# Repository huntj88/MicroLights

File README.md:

When submitting to factory, make sure USER.1 kicad layer is included in v-cut layers. On JLCPCB this is done with a PCB Remark note under advanced options section

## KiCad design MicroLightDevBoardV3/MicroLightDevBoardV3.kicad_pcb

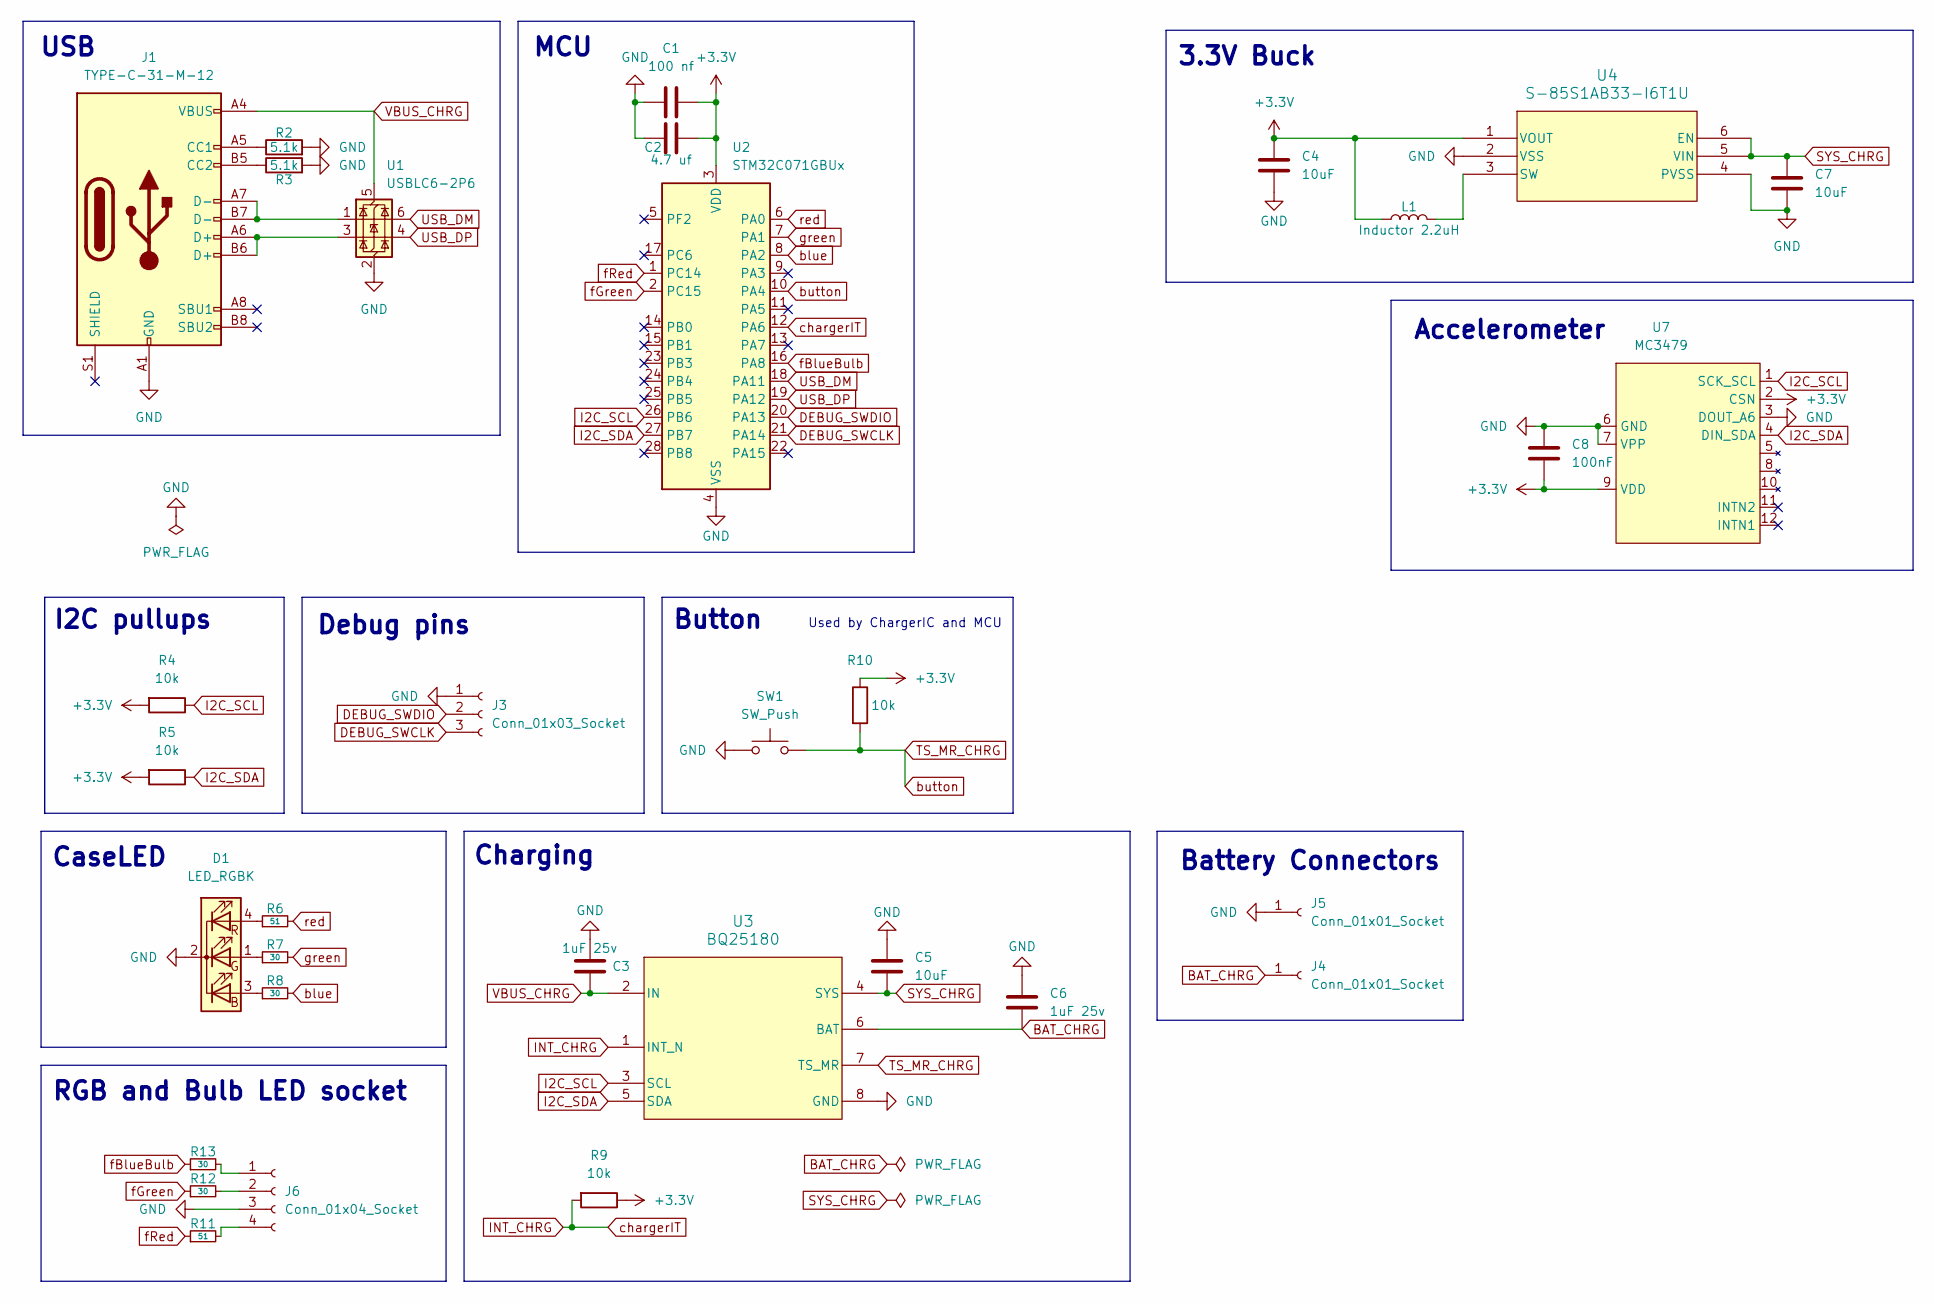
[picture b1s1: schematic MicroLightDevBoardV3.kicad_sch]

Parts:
C1: 100 nf; C_0402_1005Metric; LCSC C1525
C2: 4.7 uf; C_0402_1005Metric; LCSC C23733
C3, C6: 1uF 25v; C_0402_1005Metric; LCSC C52923
C4, C5, C7: 10uF; C_0402_1005Metric; LCSC C15525
C8: 100nF; C_0402_1005Metric; LCSC C1525
D1: LED_RGBK; RS-C1415MBAR; LCSC C2874181
J1: TYPE-C-31-M-12; USB_C_Receptacle_Hroparts_TYPE-C-31-M-12; LCSC C165948
J3: Conn_01x03_Socket; Microlight_debug_pins
J4, J5: Conn_01x01_Socket; battery_1x01_Vertical
J6: Conn_01x04_Socket; rgbLed4Pin_1.27mm
L1: Inductor 2.2uH; 74438343022_L; LCSC C337891
R2, R3: 5.1k; R_0402_1005Metric; LCSC C25905
R4, R5, R9, R10: 10k; R_0402_1005Metric; LCSC C25744
R6, R11: 51; R_0402_1005Metric; LCSC C25125
R7, R8, R12, R13: 30; R_0402_1005Metric; LCSC C270617
SW1: SW_Push; TS-1089S-02526; LCSC C455282
U1: USBLC6-2P6; SOT-666; LCSC C3647099
U2: STM32C071GBUx; QFN-28_4x4mm_P0.5mm; LCSC C42113261
U3: BQ25180; LCSC C3682423
U4: S-85S1AB33-I6T1U; SNT-6A-A-PKG_PG006-A-P-SD-2.1_ABL; LCSC C7070110
U7: MC3479; LGA-12_2x2mm_P0.5mm

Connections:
+3.3V: C1.1, C2.1, C4.1, C8.2, L1.1, R4.2, R5.2, R9.1, R10.1, U2.3 (VDD), U4.1 (VOUT), U7.2 (CSN), U7.9 (VDD)
BAT_CHRG: C6.2, J4.1, U3.6 (BAT)
DEBUG_SWCLK: J3.3, U2.21 (PA14)
DEBUG_SWDIO: J3.2, U2.20 (PA13)
GND: C1.2, C2.2, C3.1, C4.2, C5.1, C6.1, C7.2, C8.1, D1.2 (K), J1.A1 (GND), J1.B1 (GND), J3.1, J5.1, J6.3, R2.2, R3.2, SW1.1, U1.2 (GND), U2.4 (VSS), U3.8 (GND), U4.2 (VSS), U4.4 (PVSS), U7.3 (DOUT_A6), U7.6 (GND), U7.7 (VPP)
I2C_SCL: R4.1, U2.26 (PB6), U3.3 (SCL), U7.1 (SCK_SCL)
I2C_SDA: R5.1, U2.27 (PB7), U3.5 (SDA), U7.4 (DIN_SDA)
INT_CHRG: R9.2, U2.12 (PA6), U3.1 (INT_N)
unnamed: D1.3 (BA), R8.1
unnamed: D1.1 (GA), R7.1
unnamed: D1.4 (RA), R6.1
unnamed: J1.A5 (CC1), R2.1
unnamed: J1.B5 (CC2), R3.1
unnamed: J1.A6 (D+), J1.B6 (D+), U1.3 (I/O2)
unnamed: J1.A7 (D-), J1.B7 (D-), U1.1 (I/O1)
unnamed: J6.1, R13.2
unnamed: J6.2, R12.2
unnamed: J6.4, R11.2
unnamed: L1.2, U4.3 (SW)
SYS_CHRG: C5.2, C7.1, U3.4 (SYS), U4.5 (VIN), U4.6 (EN)
TS_MR_CHRG: R10.2, SW1.2, U2.10 (PA4), U3.7 (TS_MR)
USB_DM: U1.6 (I/O1), U2.18 (PA11)
USB_DP: U1.4 (I/O2), U2.19 (PA12)
VBUS_CHRG: C3.2, J1.A4 (VBUS), J1.B4 (VBUS), U1.5 (VBUS), U3.2 (IN)
blue: R8.2, U2.8 (PA2)
fBlueBulb: R13.1, U2.16 (PA8)
fGreen: R12.1, U2.2 (PC15)
fRed: R11.1, U2.1 (PC14)
green: R7.2, U2.7 (PA1)
red: R6.2, U2.6 (PA0)

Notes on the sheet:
Used by ChargerIC and MCU
I2C pullups
CaseLED
RGB and Bulb LED socket
USB
Charging
3.3V Buck
Accelerometer
Battery Connectors
Debug pins
Button
MCU

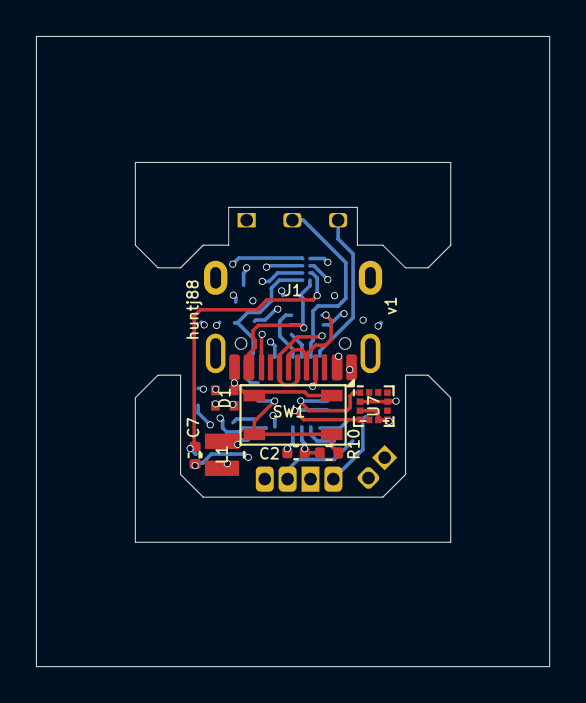
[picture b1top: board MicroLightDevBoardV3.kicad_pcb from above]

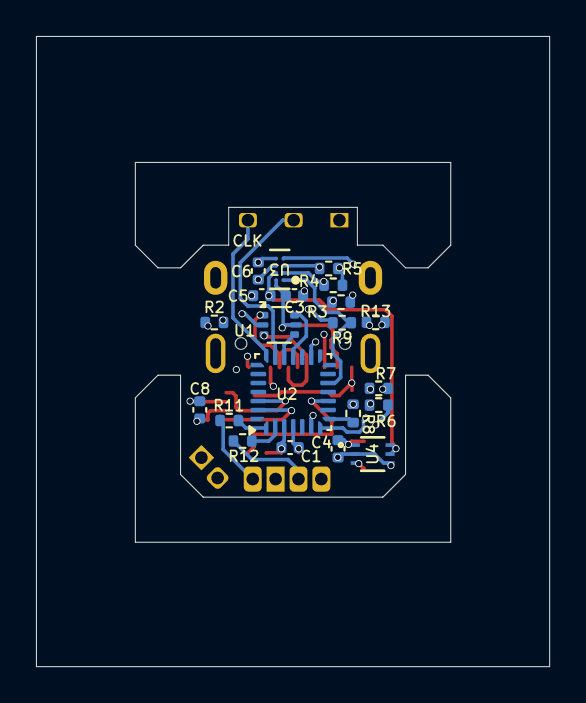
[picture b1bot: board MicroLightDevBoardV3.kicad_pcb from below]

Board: 6 copper layers, 28.5 x 35.0 mm, 33 parts (21 on the bottom side), 30 nets.

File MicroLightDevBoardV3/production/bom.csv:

Designator,Footprint,Quantity,Value,LCSC Part #
C1,0402,1,100 nf,C1525
C2,0402,1,4.7 uf,C23733
"C3, C6",0402,2,1uF 25v,C52923
"C4, C5, C7",0402,3,10uF,C15525
C8,0402,1,100nF,C1525
D1,RS-C1415MBAR,1,LED_RGBK,C2874181
J1,USB_C_Receptacle_Hroparts_TYPE-C-31-M-12,1,TYPE-C-31-M-12,C165948
L1,74438343022_L,1,Inductor 2.2uH,C337891
"R10, R4, R5, R9",0402,4,10k,C25744
"R11, R6",0402,2,51,C25125
"R12, R13, R7, R8",0402,4,30,C270617
"R2, R3",0402,2,5.1k,C25905
SW1,TS-1089S-02526,1,SW_Push,C455282
U1,SOT-666,1,USBLC6-2P6,C3647099
U2,QFN-28_4x4mm_P0.5mm,1,STM32C071GBUx,C42113261
U3,BQ25180,1,BQ25180,C3682423
U4,SNT-6A-A-PKG_PG006-A-P-SD-2.1_ABL,1,S-85S1AB33-I6T1U,C7070110
U7,LGA-12_2x2mm_P0.5mm,1,MC3479,

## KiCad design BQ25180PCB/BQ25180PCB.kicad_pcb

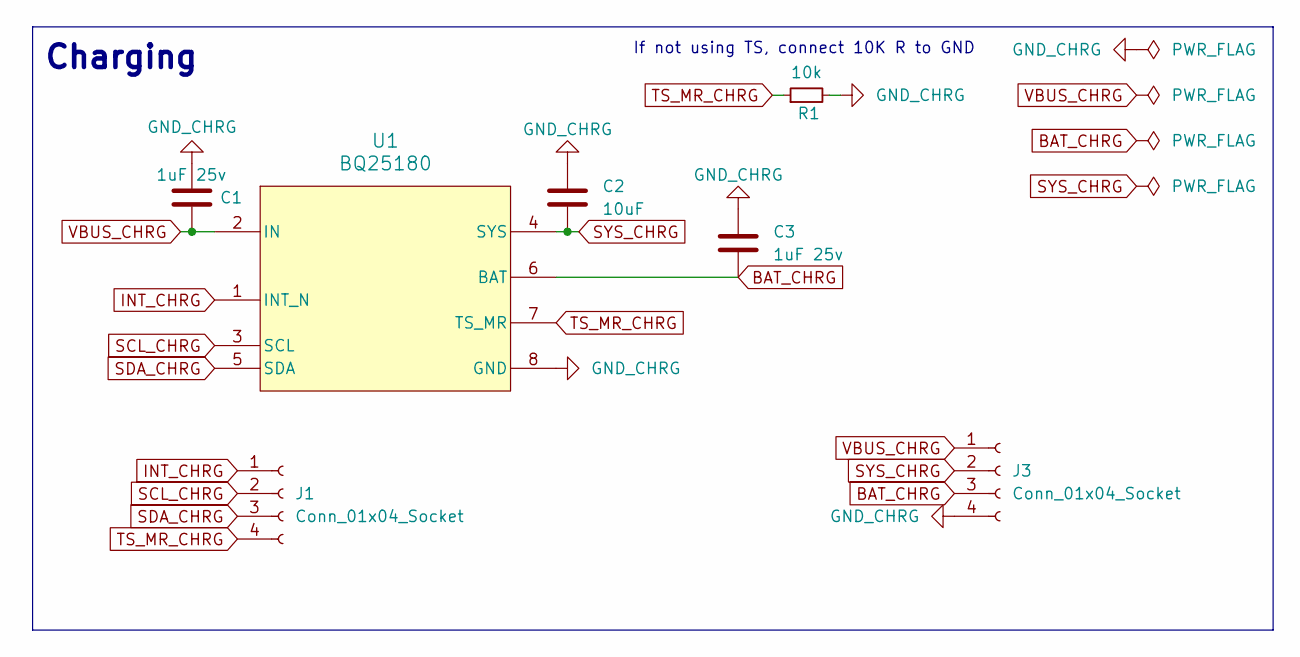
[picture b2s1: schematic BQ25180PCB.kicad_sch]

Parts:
C1, C3: 1uF 25v; C_0805_2012Metric; LCSC C1712
C2: 10uF; C_0805_2012Metric; LCSC C15850
J1, J3: Conn_01x04_Socket; PinSocket_1x04_P2.54mm_Vertical; LCSC C2718488
R1: 10k; R_0805_2012Metric; LCSC C17414
U1: BQ25180; LCSC C3682423

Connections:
BAT_CHRG: C3.2, J3.3, U1.6 (BAT)
GND_CHRG: C1.1, C2.1, C3.1, J3.4, R1.2, U1.8 (GND)
INT_CHRG: J1.1, U1.1 (INT_N)
SCL_CHRG: J1.2, U1.3 (SCL)
SDA_CHRG: J1.3, U1.5 (SDA)
SYS_CHRG: C2.2, J3.2, U1.4 (SYS)
TS_MR_CHRG: J1.4, R1.1, U1.7 (TS_MR)
VBUS_CHRG: C1.2, J3.1, U1.2 (IN)

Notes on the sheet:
If not using TS, connect 10K R to GND
Charging

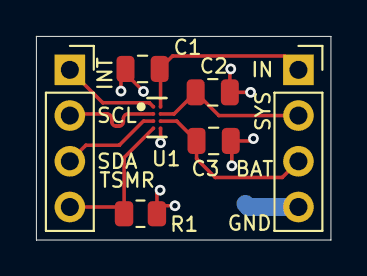
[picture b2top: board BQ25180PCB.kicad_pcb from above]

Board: 2 copper layers, 16.4 x 11.3 mm, 7 parts (0 on the bottom side), 8 nets.

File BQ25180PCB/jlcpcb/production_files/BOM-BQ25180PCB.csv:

Comment,Designator,Footprint,LCSC
10uF,C2,C_0805_2012Metric,C15850
1uF 25v,"C1,C3",C_0805_2012Metric,C1712
10k,R1,R_0805_2012Metric,C17414
Conn_01x04_Socket,"J1,J3",PinSocket_1x04_P2.54mm_Vertical,C2718488
BQ25180,U1,BQ25180,C3682423

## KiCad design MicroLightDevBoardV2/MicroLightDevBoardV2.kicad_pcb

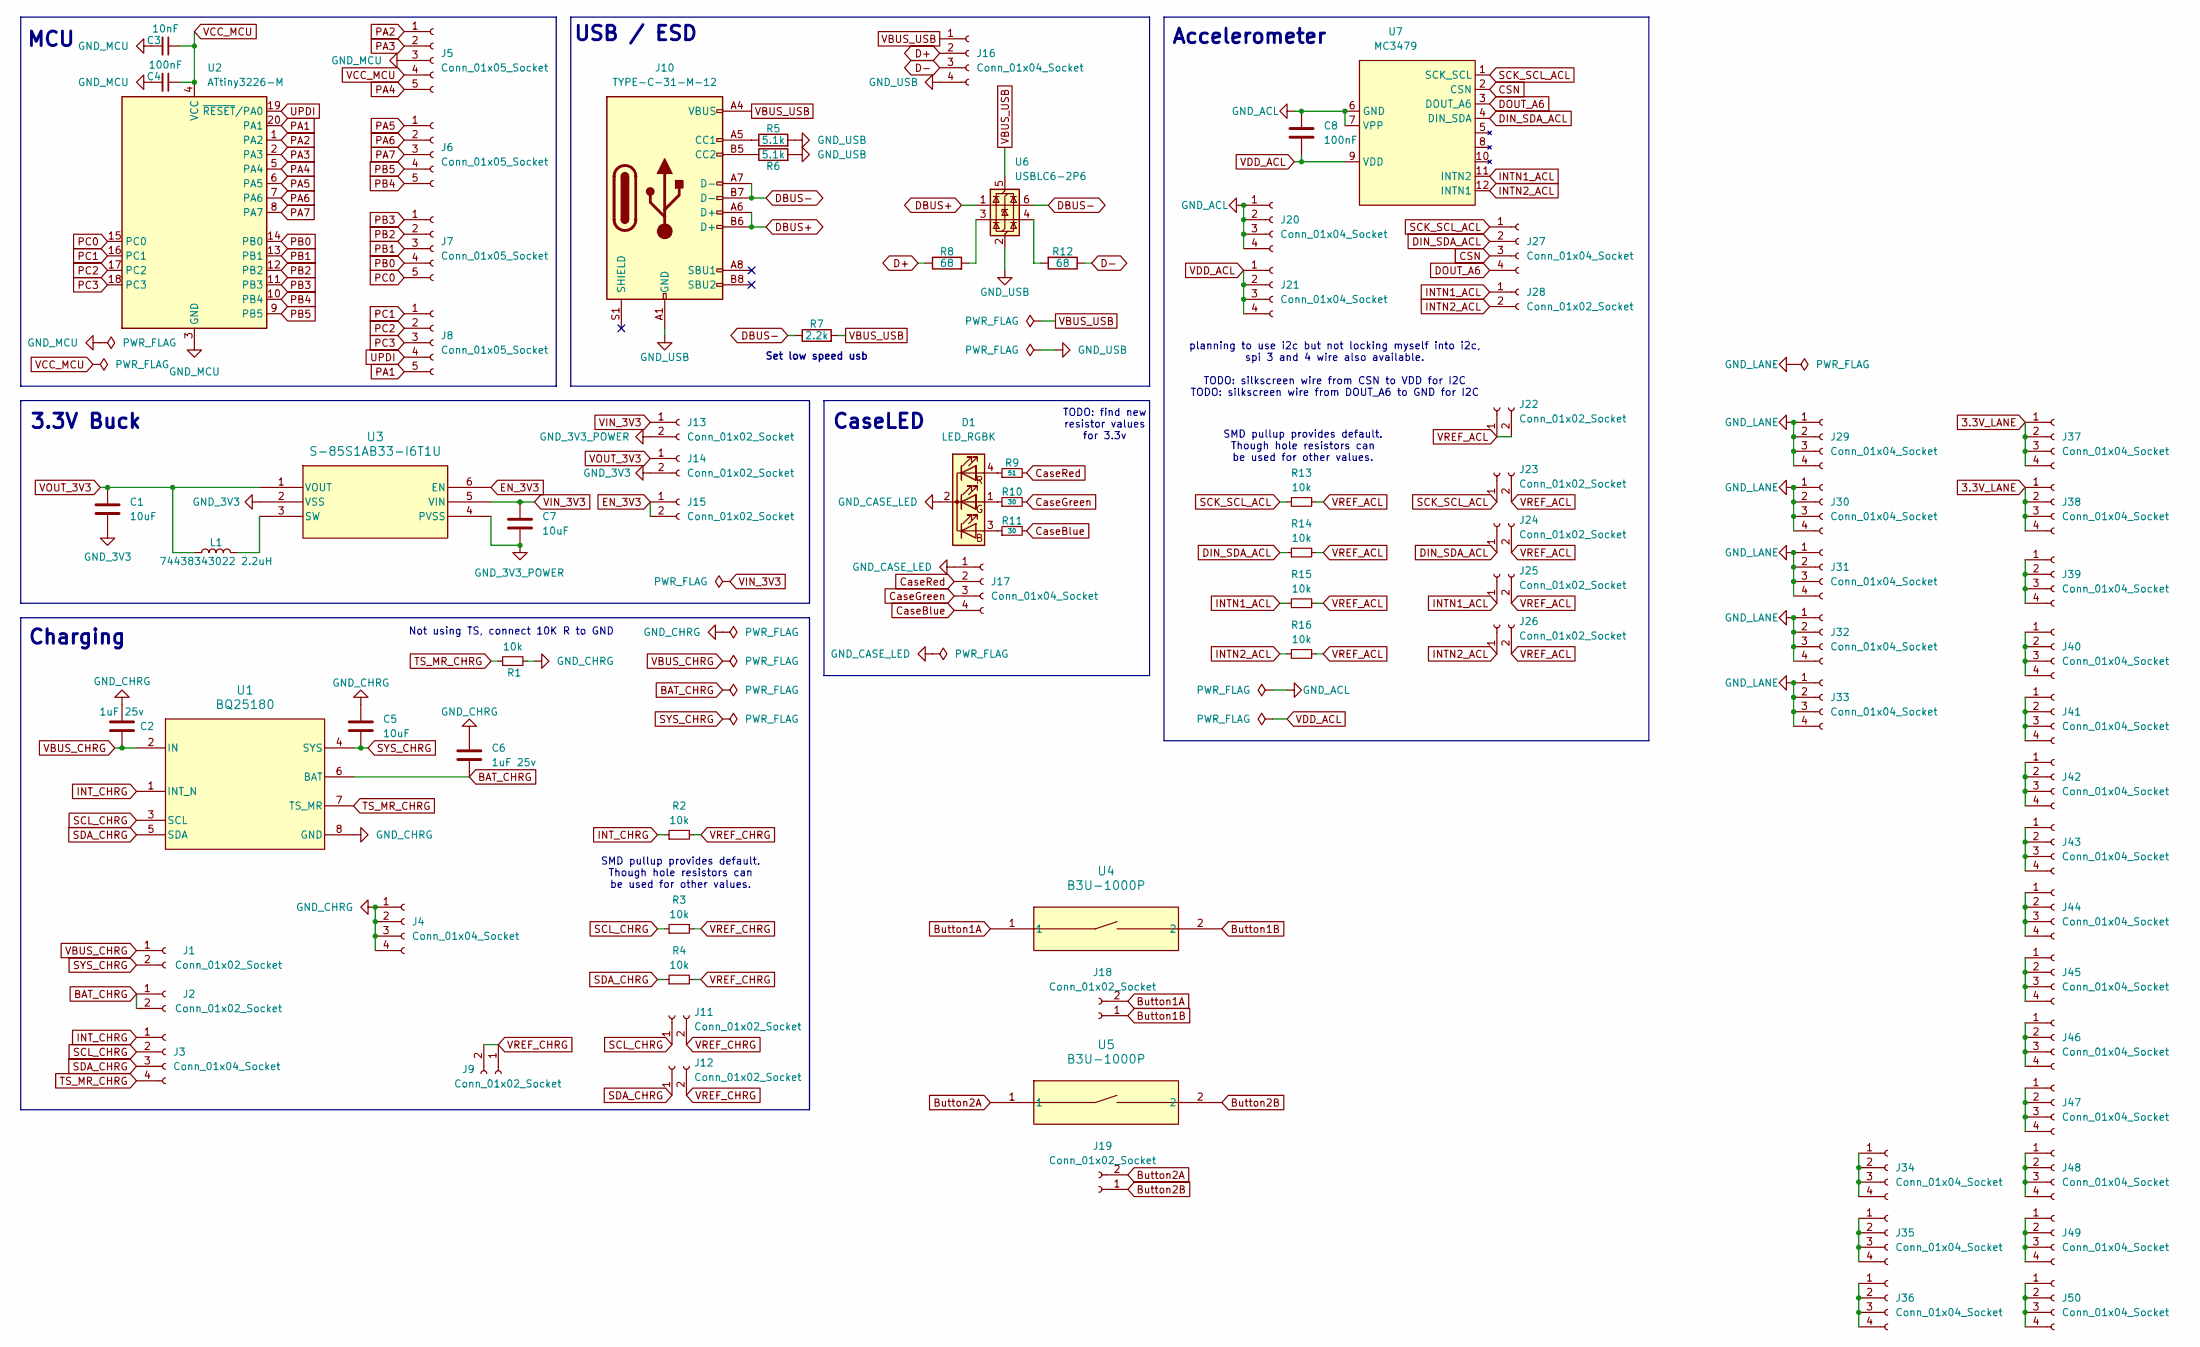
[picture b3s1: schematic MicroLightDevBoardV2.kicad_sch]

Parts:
C1, C5, C7: 10uF; C_0603_1608Metric; LCSC C96446
C2, C6: 1uF 25v; C_0603_1608Metric; LCSC C15849
C3: 10nF; C_0603_1608Metric; LCSC C57112
C4, C8: 100nF; C_0603_1608Metric; LCSC C14663
D1: LED_RGBK; RS-C1415MBAR; LCSC C2874181
J1, J2, J9, J11, J12, J13, J14, J15, J18, J19, J22, J23, J24, J25, J26, J28: Conn_01x02_Socket; PinSocket_1x02_P2.54mm_Vertical; LCSC C49661
J3, J4, J16, J17, J20, J21, J27, J29, J30, J31, J32, J33, J34, J35, J36, J37, J38, J39, J40, J41, J42, J43, J44, J45, J46, J47, J48, J49, J50: Conn_01x04_Socket; PinSocket_1x04_P2.54mm_Vertical; LCSC C2718488
J5, J6, J7, J8: Conn_01x05_Socket; PinSocket_1x05_P2.54mm_Vertical; LCSC C50950
J10: TYPE-C-31-M-12; USB_C_Receptacle_Hroparts_TYPE-C-31-M-12; LCSC C165948
L1: 74438343022 2.2uH; 74438343022_L
R1, R2, R3, R4, R13, R14, R15, R16: 10k; R_0603_1608Metric; LCSC C25804
R5, R6: 5.1k; R_0603_1608Metric; LCSC C23186
R7: 2.2k; R_0603_1608Metric; LCSC C4190
R8, R12: 68; R_0603_1608Metric; LCSC C27592
R9: 51; R_0603_1608Metric; LCSC C23197
R10, R11: 30; R_0603_1608Metric; LCSC C23140
U1: BQ25180; LCSC C3682423
U2: ATtiny3226-M; VQFN-20-1EP_3x3mm_P0.4mm_EP1.7x1.7mm
U3: S-85S1AB33-I6T1U; SNT-6A-A-PKG_PG006-A-P-SD-2.1_ABL
U4, U5: B3U-1000P; LCSC C231329
U6: USBLC6-2P6; SOT-666; LCSC C15999
U7: MC3479; LGA-12_2x2mm_P0.5mm

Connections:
3.3V_LANE: J37.1, J37.2, J37.3, J37.4, J38.1, J38.2, J38.3, J38.4
BAT_CHRG: C6.2, J2.1, J2.2, U1.6 (BAT)
Button1A: J18.2, U4.1
Button1B: J18.1, U4.2
Button2A: J19.2, U5.1
Button2B: J19.1, U5.2
CSN: J27.3, U7.2 (CSN)
CaseBlue: J17.4, R11.2
CaseGreen: J17.3, R10.2
CaseRed: J17.2, R9.2
D+: J16.2, R8.1
D-: J16.3, R12.1
DBUS+: J10.A6 (D+), J10.B6 (D+), U6.1 (I/O1)
DBUS-: J10.A7 (D-), J10.B7 (D-), R7.1, U6.6 (I/O1)
DIN_SDA_ACL: J24.1, J27.2, R14.1, U7.4 (DIN_SDA)
DOUT_A6: J27.4, U7.3 (DOUT_A6)
EN_3V3: J15.1, J15.2, U3.6 (EN)
GND_3V3: C1.2, J14.2, U3.2 (VSS)
GND_3V3_POWER: C7.2, J13.2, U3.4 (PVSS)
GND_ACL: C8.1, J20.1, J20.2, J20.3, J20.4, U7.6 (GND), U7.7 (VPP)
GND_CASE_LED: D1.2 (K), J17.1
GND_CHRG: C2.1, C5.1, C6.1, J4.1, J4.2, J4.3, J4.4, R1.2, U1.8 (GND)
GND_LANE: J29.1, J29.2, J29.3, J29.4, J30.1, J30.2, J30.3, J30.4, J31.1, J31.2, J31.3, J31.4, J32.1, J32.2, J32.3, J32.4, J33.1, J33.2, J33.3, J33.4
GND_MCU: C3.2, C4.2, J5.3, U2.3 (GND), U2.21 (GND)
GND_USB: J10.A1 (GND), J10.B1 (GND), J16.4, R5.2, R6.2, U6.2 (GND)
INTN1_ACL: J25.1, J28.1, R15.1, U7.11 (INTN2)
INTN2_ACL: J26.1, J28.2, R16.1, U7.12 (INTN1)
INT_CHRG: J3.1, R2.1, U1.1 (INT_N)
unnamed: D1.3 (BA), R11.1
unnamed: D1.1 (GA), R10.1
unnamed: D1.4 (RA), R9.1
unnamed: J10.A5 (CC1), R5.1
unnamed: J10.B5 (CC2), R6.1
unnamed: J34.1, J34.2, J34.3, J34.4
unnamed: J35.1, J35.2, J35.3, J35.4
unnamed: J36.1, J36.2, J36.3, J36.4
unnamed: J39.1, J39.2, J39.3, J39.4
unnamed: J40.1, J40.2, J40.3, J40.4
unnamed: J41.1, J41.2, J41.3, J41.4
unnamed: J42.1, J42.2, J42.3, J42.4
unnamed: J43.1, J43.2, J43.3, J43.4
unnamed: J44.1, J44.2, J44.3, J44.4
unnamed: J45.1, J45.2, J45.3, J45.4
unnamed: J46.1, J46.2, J46.3, J46.4
unnamed: J47.1, J47.2, J47.3, J47.4
unnamed: J48.1, J48.2, J48.3, J48.4
unnamed: J49.1, J49.2, J49.3, J49.4
unnamed: J50.1, J50.2, J50.3, J50.4
unnamed: R8.2, U6.3 (I/O2)
unnamed: R12.2, U6.4 (I/O2)
unnamed: L1.2, U3.3 (SW)
PA1: J8.5, U2.20 (PA1)
PA2: J5.1, U2.1 (PA2)
PA3: J5.2, U2.2 (PA3)
PA4: J5.5, U2.5 (PA4)
PA5: J6.1, U2.6 (PA5)
PA6: J6.2, U2.7 (PA6)
PA7: J6.3, U2.8 (PA7)
PB0: J7.4, U2.14 (PB0)
PB1: J7.3, U2.13 (PB1)
PB2: J7.2, U2.12 (PB2)
PB3: J7.1, U2.11 (PB3)
PB4: J6.5, U2.10 (PB4)
PB5: J6.4, U2.9 (PB5)
PC0: J7.5, U2.15 (PC0)
PC1: J8.1, U2.16 (PC1)
PC2: J8.2, U2.17 (PC2)
PC3: J8.3, U2.18 (PC3)
SCK_SCL_ACL: J23.1, J27.1, R13.1, U7.1 (SCK_SCL)
SCL_CHRG: J3.2, J11.1, R3.1, U1.3 (SCL)
SDA_CHRG: J3.3, J12.1, R4.1, U1.5 (SDA)
SYS_CHRG: C5.2, J1.2, U1.4 (SYS)
TS_MR_CHRG: J3.4, R1.1, U1.7 (TS_MR)
UPDI: J8.4, U2.19 (~RESET/PA0)
VBUS_CHRG: C2.2, J1.1, U1.2 (IN)
VBUS_USB: J10.A4 (VBUS), J10.B4 (VBUS), J16.1, R7.2, U6.5 (VBUS)
VCC_MCU: C3.1, C4.1, J5.4, U2.4 (VCC)
VDD_ACL: C8.2, J21.1, J21.2, J21.3, J21.4, U7.9 (VDD)
VIN_3V3: C7.1, J13.1, U3.5 (VIN)
VOUT_3V3: C1.1, J14.1, L1.1, U3.1 (VOUT)
VREF_ACL: J22.1, J22.2, J23.2, J24.2, J25.2, J26.2, R13.2, R14.2, R15.2, R16.2
VREF_CHRG: J9.1, J9.2, J11.2, J12.2, R2.2, R3.2, R4.2

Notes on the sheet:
MCU
3.3V Buck
SMD pullup provides default. Though hole resistors can be used for other values.
Not using TS, connect 10K R to GND
USB / ESD
Accelerometer
planning to use i2c but not locking myself into i2c, spi 3 and 4 wire also available. TODO: silkscreen wire from CSN to VDD for I2C TODO: silkscreen wire from DOUT_A6 to GND for I2C
TODO: find new resistor values for 3.3v
Set low speed usb
Charging
CaseLED

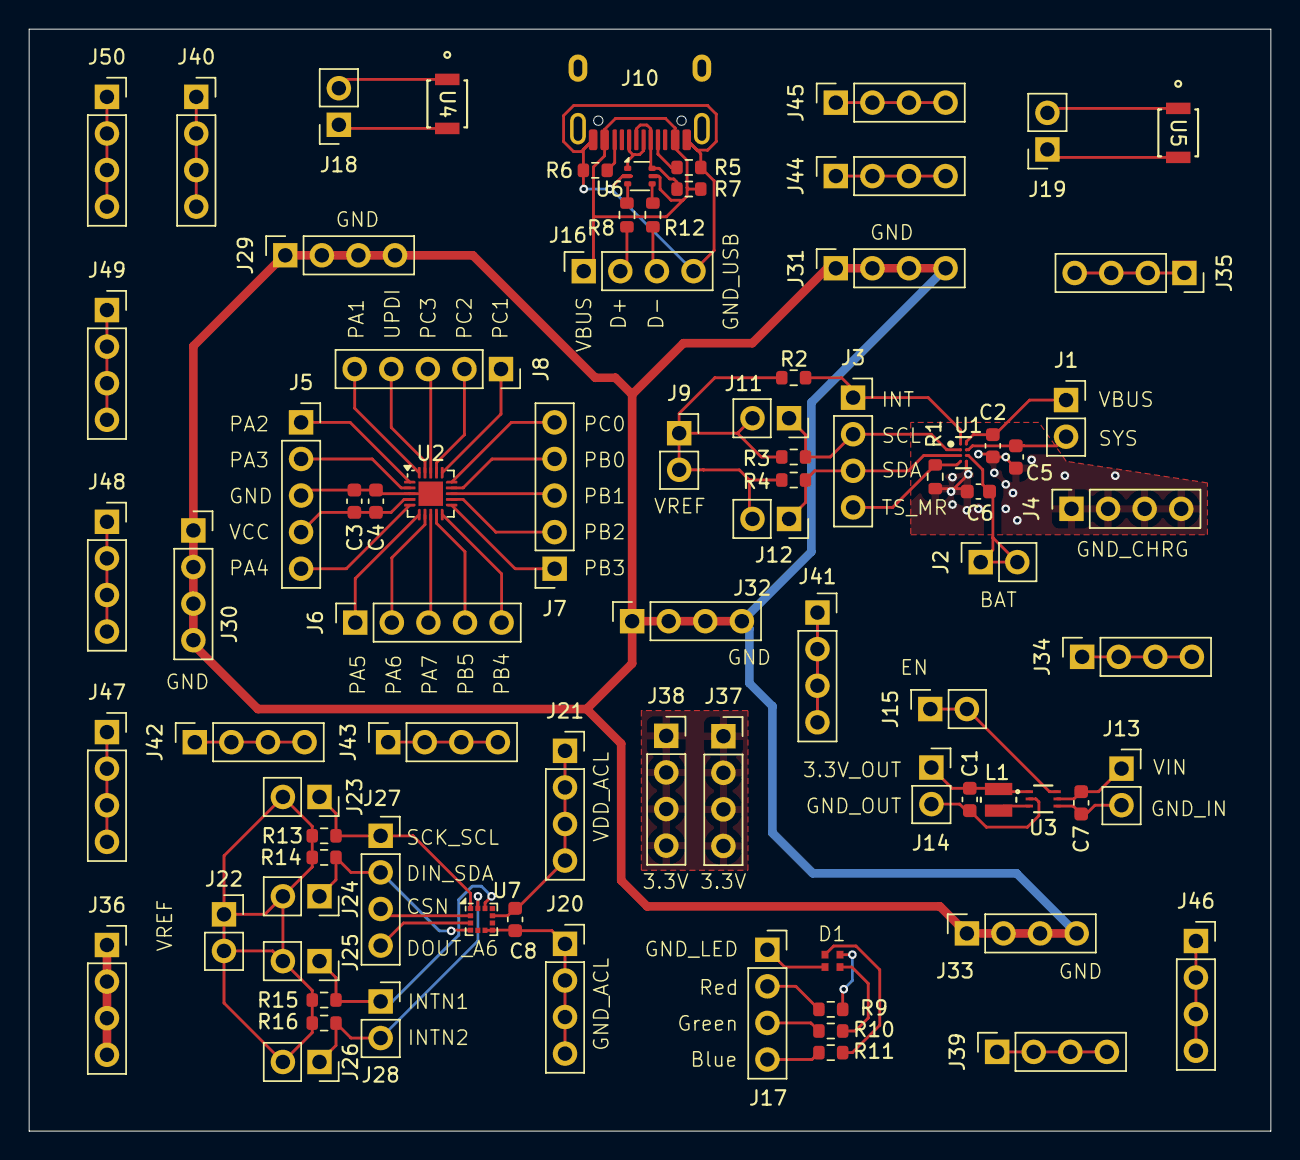
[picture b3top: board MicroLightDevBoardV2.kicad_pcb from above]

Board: 2 copper layers, 86.2 x 76.5 mm, 83 parts (0 on the bottom side), 82 nets.

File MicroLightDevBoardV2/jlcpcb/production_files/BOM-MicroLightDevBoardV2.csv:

Comment,Designator,Footprint,LCSC
100nF,"C4,C8",C_0603_1608Metric,C14663
1uF 25v,"C2,C6",C_0603_1608Metric,C15849
USBLC6-2P6,U6,SOT-666,C15999
TYPE-C-31-M-12,J10,USB_C_Receptacle_Hroparts_TYPE-C-31-M-12,C165948
B3U-1000P,"U4,U5",B3U-1000P,C231329
30,"R10,R11",R_0603_1608Metric,C23140
5.1k,"R5,R6",R_0603_1608Metric,C23186
51,R9,R_0603_1608Metric,C23197
10k,"R1,R13,R14,R15,R16,R2,R3,R4",R_0603_1608Metric,C25804
Conn_01x04_Socket,"J16,J17,J20,J21,J27,J29,J3,J30,J31,J32,J33,J34,J35,J36,J37,J38,J39,J4,J40,J41,J42,J43,J44,J45,J46,J47,J48,J49,J50",PinSocket_1x04_P2.54mm_Vertical,C2718488
68,"R12,R8",R_0603_1608Metric,C27592
LED_RGBK,D1,RS-C1415MBAR,C2874181
BQ25180,U1,BQ25180,C3682423
2.2k,R7,R_0603_1608Metric,C4190
Conn_01x02_Socket,"J1,J11,J12,J13,J14,J15,J18,J19,J2,J22,J23,J24,J25,J26,J28,J9",PinSocket_1x02_P2.54mm_Vertical,C49661
Conn_01x05_Socket,"J5,J6,J7,J8",PinSocket_1x05_P2.54mm_Vertical,C50950
10nF,C3,C_0603_1608Metric,C57112
10uF,"C1,C5,C7",C_0603_1608Metric,C96446
74438343022 2.2uH,L1,74438343022_L,
S-85S1AB33-I6T1U,U3,SNT-6A-A-PKG_PG006-A-P-SD-2.1_ABL,
MC3479,U7,LGA-12_2x2mm_P0.5mm,
ATtiny3226-M,U2,VQFN-20-1EP_3x3mm_P0.4mm_EP1.7x1.7mm,

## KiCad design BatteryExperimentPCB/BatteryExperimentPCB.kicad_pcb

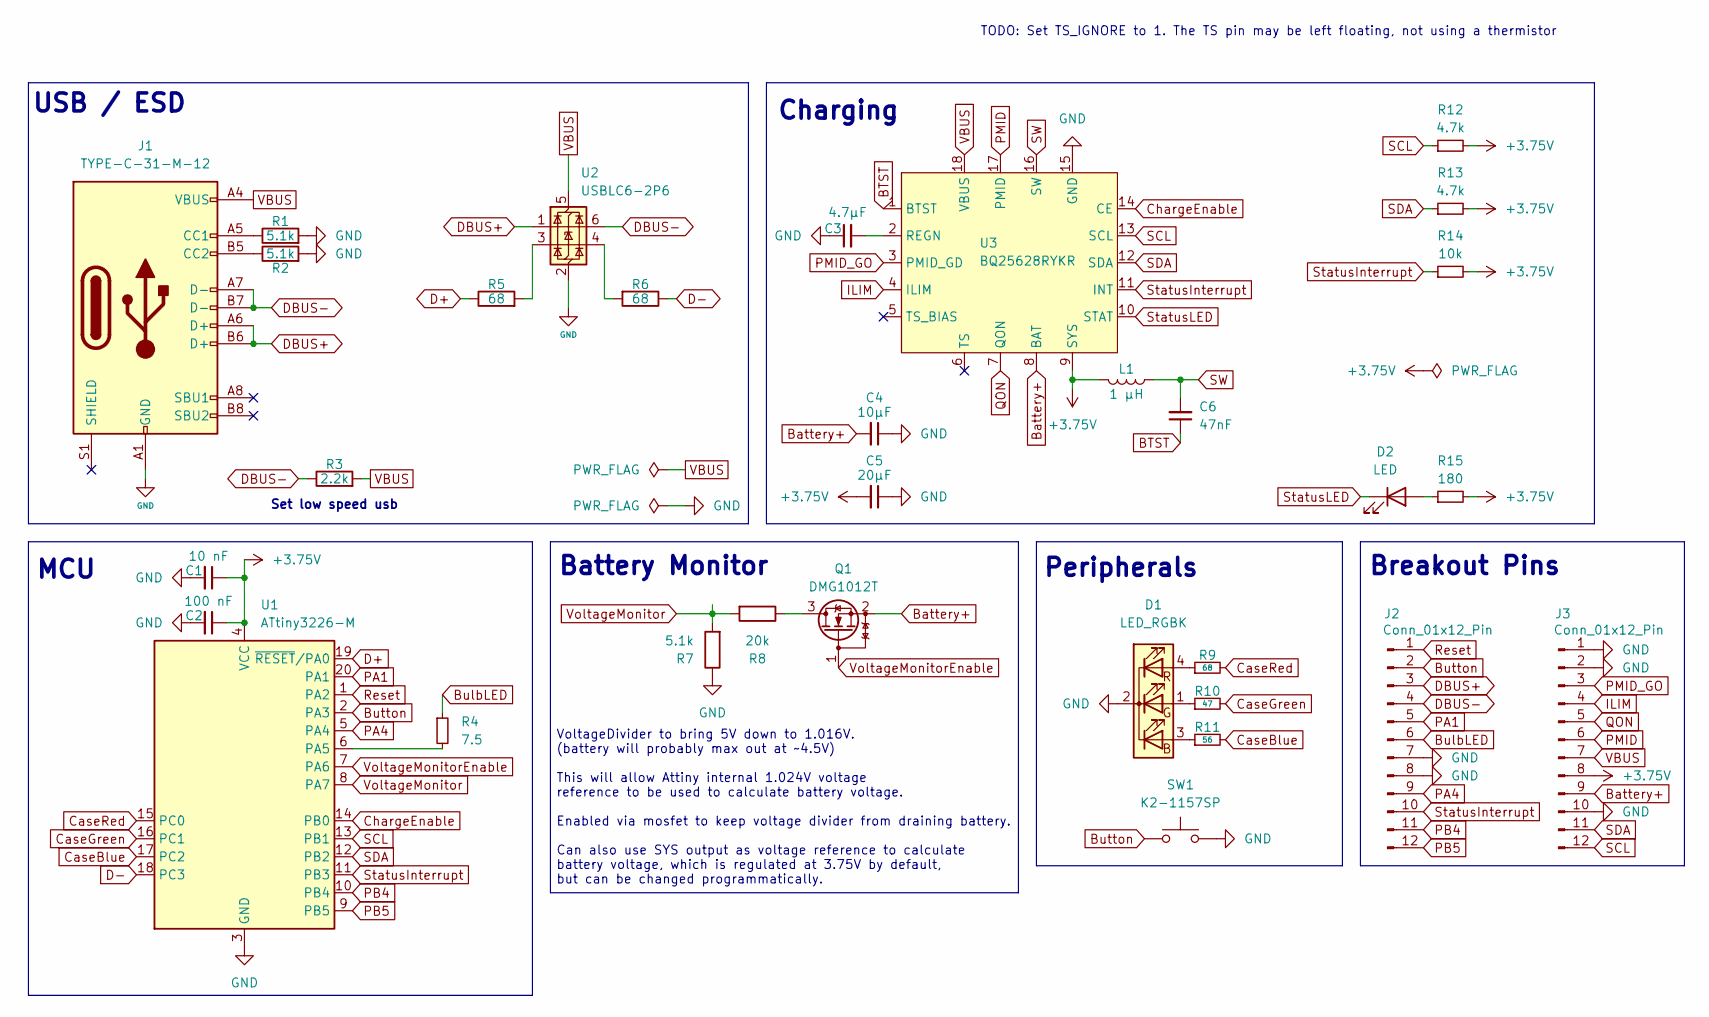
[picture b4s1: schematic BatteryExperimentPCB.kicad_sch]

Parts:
C1: 10 nF; C_0603_1608Metric
C2: 100 nF; C_0603_1608Metric
C3: 4.7μF; C_0603_1608Metric
C4: 10μF; C_0603_1608Metric
C5: 20μF; C_0603_1608Metric
C6: 47nF; C_0603_1608Metric
D1: LED_RGBK; RS-C1415MBAR
D2: LED; LED_0805_2012Metric
J1: TYPE-C-31-M-12; USB_C_Receptacle_Hroparts_TYPE-C-31-M-12
J2, J3: Conn_01x12_Pin; PinHeader_1x12_P2.54mm_Vertical
L1: 1 μH; L_0805_2012Metric
Q1: DMG1012T; SOT-523
R1, R2, R7: 5.1k; R_0603_1608Metric
R3: 2.2k; R_0603_1608Metric
R4: 7.5; R_0603_1608Metric
R5, R6, R9: 68; R_0603_1608Metric
R8: 20k; R_0603_1608Metric
R10: 47; R_0603_1608Metric
R11: 56; R_0603_1608Metric
R12, R13: 4.7k; R_0603_1608Metric
R14: 10k; R_0603_1608Metric
R15: 180; R_0603_1608Metric
SW1: K2-1157SP
U1: ATtiny3226-M; VQFN-20-1EP_3x3mm_P0.4mm_EP1.7x1.7mm
U2: USBLC6-2P6; SOT-666
U3: BQ25628RYKR; RYK0018A-MFG

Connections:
+3.75V: C1.1, C2.1, C5.2, J3.8, L1.2, R12.2, R13.2, R14.2, R15.2, U1.4 (VCC), U3.9 (SYS)
BTST: C6.1, U3.1 (BTST)
Battery+: C4.2, J3.9, Q1.2 (S), U3.8 (BAT)
BulbLED: J2.6, R4.1
Button: J2.2, SW1.1, U1.2 (PA3)
CaseBlue: R11.2, U1.17 (PC2)
CaseGreen: R10.2, U1.16 (PC1)
CaseRed: R9.2, U1.15 (PC0)
ChargeEnable: U1.14 (PB0), U3.14 (CE)
D+: R5.1, U1.19 (~RESET/PA0)
D-: R6.1, U1.18 (PC3)
DBUS+: J1.A6 (D+), J1.B6 (D+), J2.3, U2.1 (I/O1)
DBUS-: J1.A7 (D-), J1.B7 (D-), J2.4, R3.1, U2.6 (I/O1)
GND: C1.2, C2.2, C3.1, C4.1, C5.1, D1.2 (K), J1.A1 (GND), J1.B1 (GND), J2.7, J2.8, J3.1, J3.2, J3.10, R1.2, R2.2, R7.1, SW1.2, U1.3 (GND), U1.21 (GND), U2.2 (GND), U3.15 (GND)
ILIM: J3.4, U3.4 (ILIM)
unnamed: D1.3 (BA), R11.1
unnamed: D1.1 (GA), R10.1
unnamed: D1.4 (RA), R9.1
unnamed: D2.2 (A), R15.1
unnamed: J1.A5 (CC1), R1.1
unnamed: J1.B5 (CC2), R2.1
unnamed: Q1.3 (D), R8.1
unnamed: R5.2, U2.3 (I/O2)
unnamed: R6.2, U2.4 (I/O2)
unnamed: R4.2, U1.6 (PA5)
unnamed: C3.2, U3.2 (REGN)
PA1: J2.5, U1.20 (PA1)
PA4: J2.9, U1.5 (PA4)
PB4: J2.11, U1.10 (PB4)
PB5: J2.12, U1.9 (PB5)
PMID: J3.6, U3.17 (PMID)
PMID_GO: J3.3, U3.3 (PMID_GD)
QON: J3.5, U3.7 (QON)
Reset: J2.1, U1.1 (PA2)
SCL: J3.12, R12.1, U1.13 (PB1), U3.13 (SCL)
SDA: J3.11, R13.1, U1.12 (PB2), U3.12 (SDA)
SW: C6.2, L1.1, U3.16 (SW)
StatusInterrupt: J2.10, R14.1, U1.11 (PB3), U3.11 (INT)
StatusLED: D2.1 (K), U3.10 (STAT)
VBUS: J1.A4 (VBUS), J1.B4 (VBUS), J3.7, R3.2, U2.5 (VBUS), U3.18 (VBUS)
VoltageMonitor: R7.2, R8.2, U1.8 (PA7)
VoltageMonitorEnable: Q1.1 (G), U1.7 (PA6)

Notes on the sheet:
Peripherals
Set low speed usb
TODO: Set TS_IGNORE to 1. The TS pin may be left floating, not using a thermistor
USB / ESD
MCU
VoltageDivider to bring 5V down to 1.016V. (battery will probably max out at ~4.5V) This will allow Attiny internal 1.024V voltage reference to be used to calculate battery voltage. Enabled via mosfet to keep voltage divider from draining battery. Can also use SYS output as voltage reference to cal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
Charging
Breakout Pins
Battery Monitor

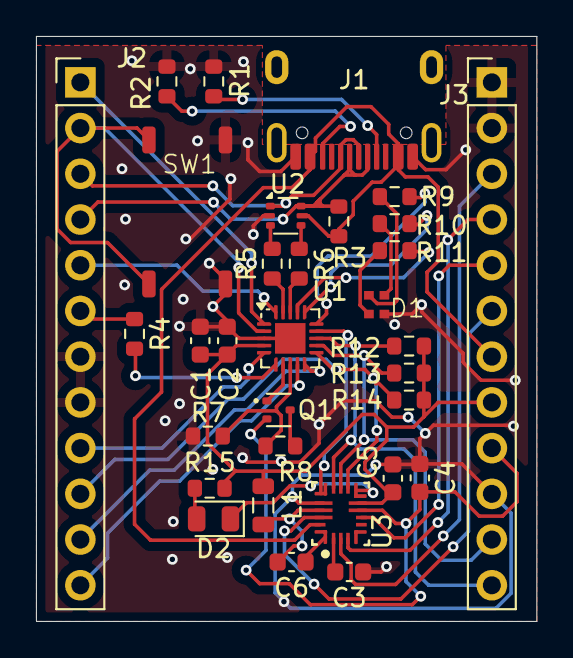
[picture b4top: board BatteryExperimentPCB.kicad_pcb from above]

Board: 2 copper layers, 27.8 x 32.5 mm, 32 parts (0 on the bottom side), 42 nets.

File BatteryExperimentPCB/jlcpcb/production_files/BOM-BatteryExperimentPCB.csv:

Comment,Designator,Footprint,LCSC
100 nF,C2,C_0603_1608Metric,C14663
USBLC6-2P6,U2,SOT-666,C15999
47nF,C6,C_0603_1608Metric,C1622
TYPE-C-31-M-12,J1,USB_C_Receptacle_Hroparts_TYPE-C-31-M-12,C165948
 4.7μF,C3,C_0603_1608Metric,C19666
10μF,C4,C_0603_1608Metric,C19702
DMG1012T,Q1,SOT-523,C20512
7.5,R4,R_0603_1608Metric,C22859
LED,D2,LED_0805_2012Metric,C2296
4.7k,"R12,R13",R_0603_1608Metric,C23162
5.1k,"R1,R2,R7",R_0603_1608Metric,C23186
10k,R14,R_0603_1608Metric,C25804
K2-1157SP,SW1,K2-1157SP,C2909692
ATtiny3226-M,U1,VQFN-20-1EP_3x3mm_P0.4mm_EP1.7x1.7mm,C3216895
20k,R8,R_0603_1608Metric,C4184
2.2k,R3,R_0603_1608Metric,C4190
68,"R5,R6",R_0603_1608Metric,C4275
10 nF,C1,C_0603_1608Metric,C57112
20μF,C5,C_0603_1608Metric,C59461
BQ25628RYKR,U3,RYK0018A-MFG,C6055599
1 μH,L1,L_0805_2012Metric,C7588890
180,R15,R_0603_1608Metric,C8218
Conn_01x12_Pin,J2,PinHeader_1x12_P2.54mm_Vertical,
Conn_01x12_Pin,J3,PinHeader_1x12_P2.54mm_Vertical,
56,R11,R_0603_1608Metric,
47,R10,R_0603_1608Metric,
68,R9,R_0603_1608Metric,
LED_RGBK,D1,RS-C1415MBAR,

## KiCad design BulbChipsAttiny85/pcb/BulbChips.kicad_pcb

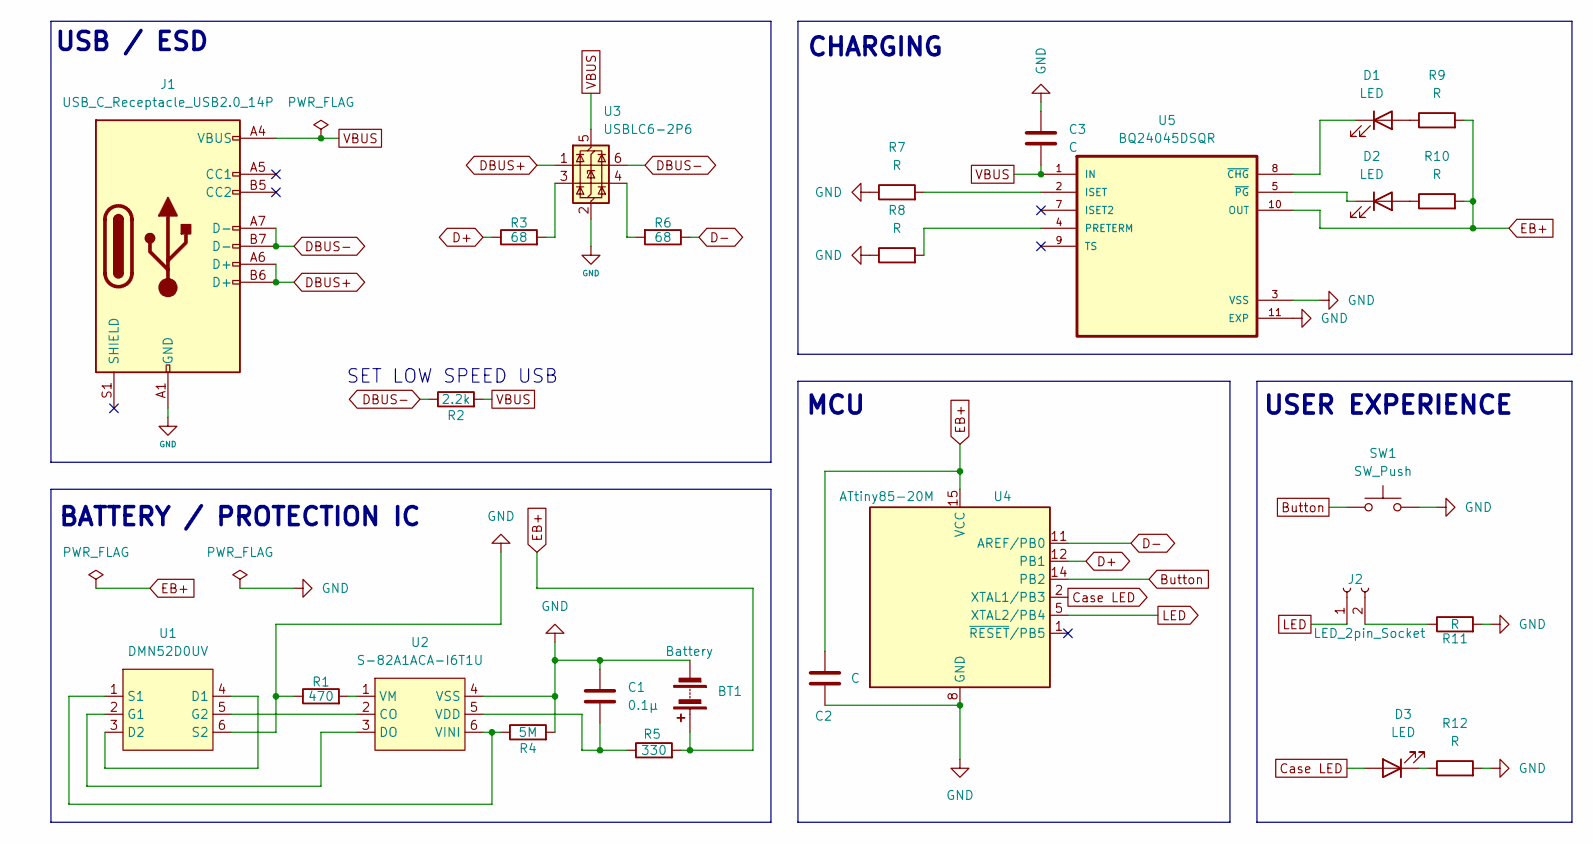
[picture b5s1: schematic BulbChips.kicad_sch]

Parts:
BT1: Battery; PinHeader_1x02_P2.54mm_Vertical_SMD_Pin1Left
C1: 0.1μ; C_0201_0603Metric
C2, C3: C; C_0201_0603Metric
D1, D2, D3: LED; LED_0201_0603Metric
J1: USB_C_Receptacle_USB2.0_14P; USB_C_Receptacle_G-Switch_GT-USB-7025
J2: LED_2pin_Socket; PinHeader_1x02_P2.54mm_Vertical_SMD_Pin1Right
R1: 470; R_0201_0603Metric
R2: 2.2k; R_0201_0603Metric
R3, R6: 68; R_0201_0603Metric
R4: 5M; R_0201_0603Metric
R5: 330; R_0201_0603Metric
R7, R8, R9, R10, R11, R12: R; R_0201_0603Metric
SW1: SW_Push; SW_SPST_PTS810
U1: DMN52D0UV; SOT-563
U2: S-82A1ACA-I6T1U; SNT-6A
U3: USBLC6-2P6; SOT-666
U4: ATtiny85-20M; QFN-20-1EP_4x4mm_P0.5mm_EP2.6x2.6mm
U5: BQ24045DSQR; WSON-10-1EP_2x3mm_P0.5mm_EP0.84x2.4mm_ThermalVias

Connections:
Button: SW1.1, U4.14 (PB2)
Case LED: D3.2 (A), U4.2 (XTAL1/PB3)
D+: R3.1, U4.12 (PB1)
D-: R6.1, U4.11 (AREF/PB0)
DBUS+: J1.A6 (D+), J1.B6 (D+), U3.1 (I/O1)
DBUS-: J1.A7 (D-), J1.B7 (D-), R2.1, U3.6 (I/O1)
EB+: BT1.1 (+), C2.1, R5.2, R9.2, R10.2, U4.15 (VCC), U5.10 (OUT)
GND: BT1.2 (-), C1.1, C2.2, C3.1, J1.A1 (GND), J1.A12 (GND), J1.B1 (GND), J1.B12 (GND), R1.1, R4.2, R7.1, R8.1, R11.2, R12.2, SW1.2, U1.6 (S2), U2.4 (VSS), U3.2 (GND), U4.8 (GND), U4.21 (GND), U5.3 (VSS), U5.11 (EXP)
LED: J2.1, U4.5 (XTAL2/PB4)
unnamed: D1.2 (A), R9.1
unnamed: D1.1 (K), U5.8 (~CHG)
unnamed: D2.2 (A), R10.1
unnamed: D2.1 (K), U5.5 (~PG)
unnamed: D3.1 (K), R12.1
unnamed: J2.2, R11.1
unnamed: R3.2, U3.3 (I/O2)
unnamed: R6.2, U3.4 (I/O2)
unnamed: U1.3 (D2), U1.4 (D1)
unnamed: U1.2 (G1), U2.3 (DO)
unnamed: U1.5 (G2), U2.2 (CO)
unnamed: R4.1, U1.1 (S1), U2.6 (VINI)
unnamed: C1.2, R5.1, U2.5 (VDD)
unnamed: R1.2, U2.1 (VM)
unnamed: R7.2, U5.2 (ISET)
unnamed: R8.2, U5.4 (PRETERM)
VBUS: C3.2, J1.A4 (VBUS), J1.A9 (VBUS), J1.B4 (VBUS), J1.B9 (VBUS), R2.2, U3.5 (VBUS), U5.1 (IN)

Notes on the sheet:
SET LOW SPEED USB
BATTERY / PROTECTION IC
CHARGING
USER EXPERIENCE
USB / ESD
MCU

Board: 2 copper layers, 27 parts (0 on the bottom side), 26 nets, no tracks yet.

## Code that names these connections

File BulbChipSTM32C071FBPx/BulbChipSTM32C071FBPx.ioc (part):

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Mcu.Name=STM32C071FBPx
Mcu.Package=TSSOP20_GP
Mcu.UserName=STM32C071FBPx
PA0.GPIOParameters=GPIO_Label
PA0.GPIO_Label=red
PA0.Signal=S_TIM1_CH1
PA1.GPIOParameters=GPIO_Label
PA1.GPIO_Label=green
PA1.Signal=S_TIM1_CH2
PA11\ [PA9].Mode=Device
PA11\ [PA9].Signal=USB_DM
PA12\ [PA10].Mode=Device
PA12\ [PA10].Signal=USB_DP
PA13.Mode=Serial_Wire
PA13.Signal=DEBUG_SWDIO
PA14-BOOT0.Mode=Serial_Wire
PA14-BOOT0.Signal=DEBUG_SWCLK
PA14-BOOT0__PA15.StandardMode=true
PA2.GPIOParameters=GPIO_Label
PA2.GPIO_Label=blue
PA2.Signal=S_TIM1_CH3
PA4.GPIOParameters=GPIO_PuPd,GPIO_Label,GPIO_ModeDefaultEXTI
PA4.GPIO_Label=button
PA4.GPIO_ModeDefaultEXTI=GPIO_MODE_IT_FALLING
PA4.GPIO_PuPd=GPIO_NOPULL
PA4.Signal=GPXTI4
PA5.GPIOParameters=GPIO_Label
PA5.GPIO_Label=bulbLed
PA5.Signal=GPIO_Output
PA6.GPIOParameters=GPIO_Label,GPIO_ModeDefaultEXTI
PA6.GPIO_Label=chargerIT
PA6.GPIO_ModeDefaultEXTI=GPIO_MODE_IT_FALLING
PA6.Signal=GPXTI6
PA8.GPIOParameters=GPIO_Label
PA8.GPIO_Label=fBlue
PA8.Signal=S_TIM3_CH4
PB3__PB4__PB5__PB6.StandardMode=true
PB6.Mode=I2C
PB6.Signal=I2C1_SCL
PB7.Mode=I2C
PB7.Signal=I2C1_SDA
PB7__PB8.StandardMode=true
PC14-OSCX_IN(PC14).GPIOParameters=GPIO_Label
PC14-OSCX_IN(PC14).GPIO_Label=fRed
PC14-OSCX_IN(PC14).Signal=S_TIM3_CH2
PC15-OSCX_OUT(PC15).GPIOParameters=GPIO_Label
PC15-OSCX_OUT(PC15).GPIO_Label=fGreen
PC15-OSCX_OUT(PC15).Signal=S_TIM3_CH3
RCC.HSE_VALUE=8000000
RCC.SYSCLKFreq_VALUE=12000000
board=custom
